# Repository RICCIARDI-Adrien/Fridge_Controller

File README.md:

# Fridge controller

A very simple controller with a light electronic BoM. It manages the fridge temperature with hardcoded thresholds and hysteresis.

## Project information

The board is powered by a PIC12F683 MCU. It samples the fridge or freezer temperature through a NTC sensor. It then controls the fridge cold unit through a 230V/12A relay.

### Hardware

The board schematic and PCB are designed with KiCad 6.

### Firmware

The microcontroller firmware is compiled with the free version of Microchip XC8 compiler.

## Photo gallery

Naked PCB :

Assembled PCB :

Connector adapters for the targeted freezer :

Transparent plastic casing (reference Deltron 479-0160-0) :

Board inside the casing with drilled holes and connector adapters :

The board controlling the freezer in a basement :

## Technical information about the Brandt UD2321 freezer

The following information have been found through reverse engineering, so be careful about their accuracy !  

The picture below shows the connector names (the names are taken from the original controller board PCB).  
There were no indications on the PCB of the pin numbers, so I assigned them myself.

Connector CN1 signals :
| Pin number | Description             |
| ---------- | ----------------------- |
| 1          | Not connected           |
| 2          | Not connected           |
| 3          | Original controller GND |
| 4          | NTC (thermal sensor)    |

Connector CN2 signals :
| Pin number | Description          |
| ---------- | -------------------- |
| 1          | Cold unit (note 1)   |
| 2          | Cold unit (note 1)   |
| 3          | Not connected        |
| 4          | Not connected        |
| 5          | Door switch (note 2) |
| 6          | 230V neutral         |
| 7          | Door switch (note 3) |
| 8          | 230V live            |

Notes :
1. Connect CN2 pins 1 and 2 to neutral to start the cold unit.
2. Door switch contact is normally closed.
3. CN2 pin 7 is connected the 230V live on the original controller board.

Connector CN3 is not populated.

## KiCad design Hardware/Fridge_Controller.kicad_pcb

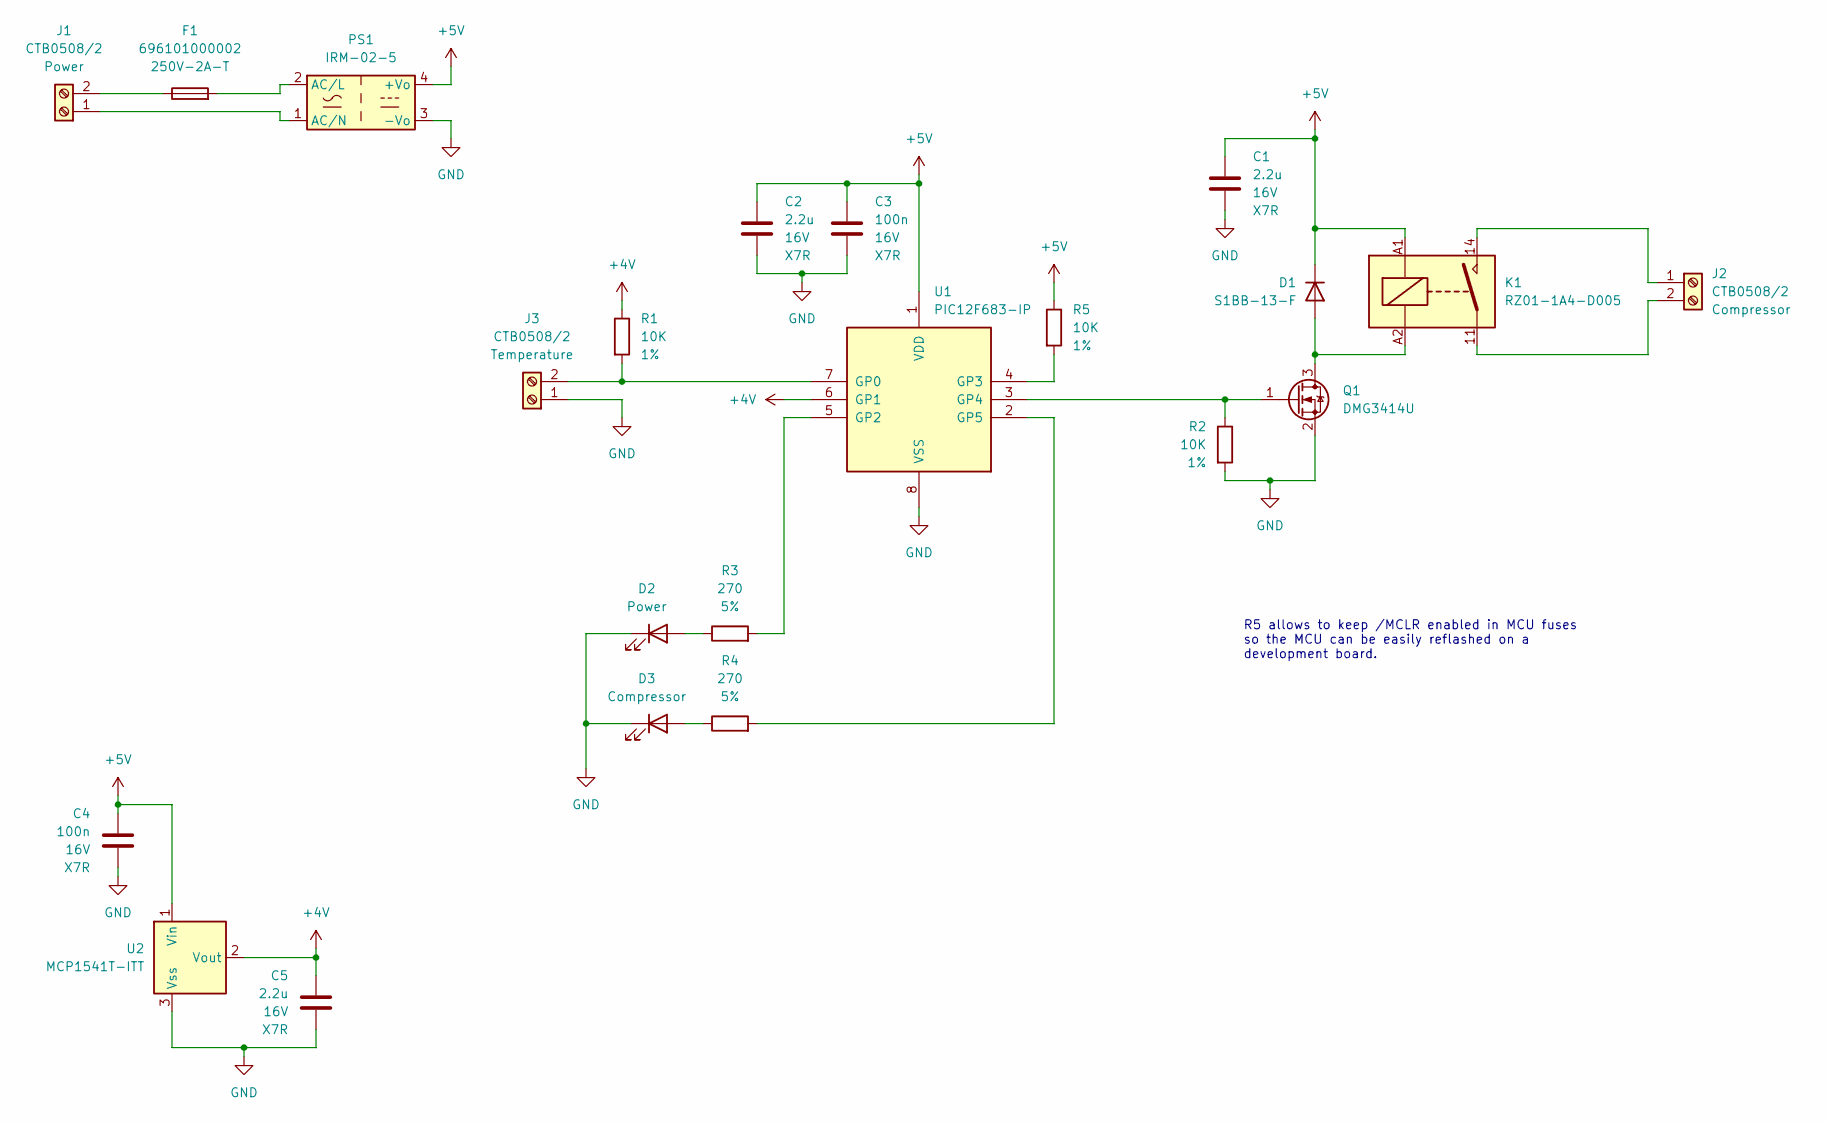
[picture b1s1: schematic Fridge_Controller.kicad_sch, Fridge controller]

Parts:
C1, C2, C5: 2.2u; C_0805_2012Metric_Pad1.18x1.45mm_HandSolder
C3, C4: 100n; C_0603_1608Metric_Pad1.08x0.95mm_HandSolder
D1: S1BB-13-F; D_SMB_Handsoldering
D2: Power; LED_D5.0mm
D3: Compressor; LED_D5.0mm
F1: 696101000002; Fuseholder_Cylinder-5x20mm_Stelvio-Kontek_PTF78_Horizontal_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
J1, J2, J3: CTB0508/2; TerminalBlock_bornier-2_P5.08mm
K1: RZ01-1A4-D005
PS1: IRM-02-5; Converter_ACDC_MeanWell_IRM-02-xx_THT
Q1: DMG3414U; SOT-23
R1, R2, R5: 10K; R_0603_1608Metric_Pad0.98x0.95mm_HandSolder
R3, R4: 270; R_1206_3216Metric_Pad1.30x1.75mm_HandSolder
U1: PIC12F683-IP; DIP-8_W7.62mm
U2: MCP1541T-ITT; SOT-23

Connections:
+4V: C5.1, R1.1, U1.6 (GP1), U2.2 (Vout)
+5V: C1.1, C2.1, C3.1, C4.1, D1.1 (K), K1.A1, PS1.4 (+Vo), R5.1, U1.1 (VDD), U2.1 (Vin)
GND: C1.2, C2.2, C3.2, C4.2, C5.2, D2.1 (K), D3.1 (K), J3.1, PS1.3 (-Vo), Q1.2 (S), R2.2, U1.8 (VSS), U2.3 (Vss)
unnamed: D1.2 (A), K1.A2, Q1.3 (D)
unnamed: D2.2 (A), R3.1
unnamed: D3.2 (A), R4.1
unnamed: F1.1, J1.2
unnamed: F1.2, PS1.2 (AC/L)
unnamed: J1.1, PS1.1 (AC/N)
unnamed: J2.1, K1.14
unnamed: J2.2, K1.11
unnamed: J3.2, R1.2, U1.7 (GP0)
unnamed: Q1.1 (G), R2.1, U1.3 (GP4)
unnamed: R3.2, U1.5 (GP2)
unnamed: R4.2, U1.2 (GP5)
unnamed: R5.2, U1.4 (GP3)

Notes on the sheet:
R5 allows to keep /MCLR enabled in MCU fuses so the MCU can be easily reflashed on a development board.

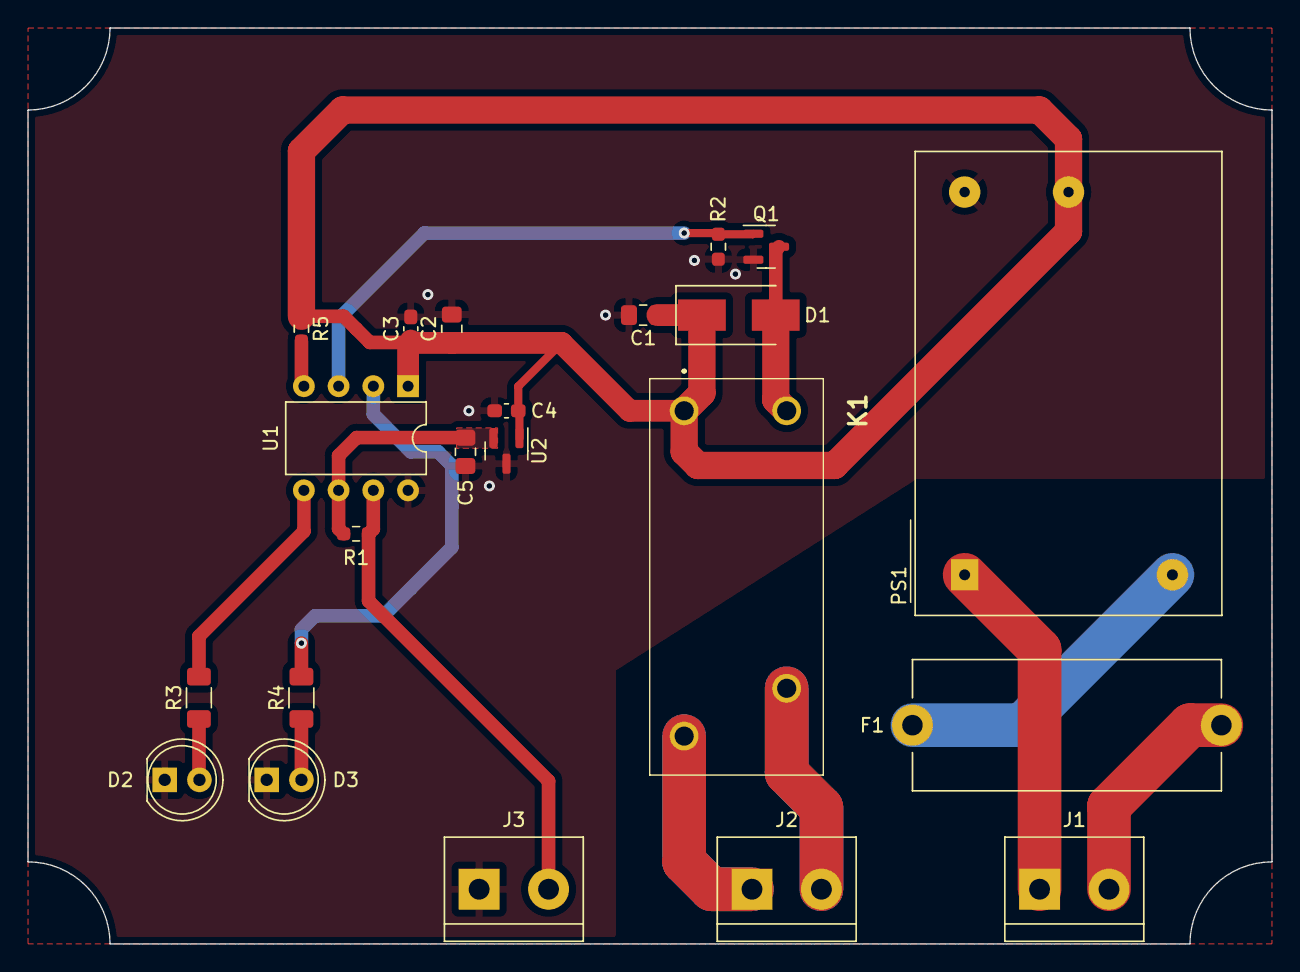
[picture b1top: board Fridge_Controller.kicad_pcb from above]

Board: 2 copper layers, 91.0 x 67.0 mm, 22 parts (0 on the bottom side), 16 nets.

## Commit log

2022-12-26 Initial commit. Added an empty KiCad project.
2022-12-26 Added MIT license.
2022-12-27 [Hardware] Added RZ01-1A4-D005 relay symbol, footprint and 3D model.
2022-12-27 [Hardware] Added schematic.
2023-01-14 [Hardware] Added fuse, fuse holder and screw terminals part references to schematics.
2023-02-02 [Hardware] Added a pull-up resistor on microcontroller /MCLR pin so the /MCLR signal can be left active in the MCU fuses and the MCU can be more easily reflashed when inserted on a development board.
2023-02-02 [Firmware] Started firmware implementation. Added microcontroller fuses configuration.
2023-02-18 [Firmware] Switched microcontroller clock speed to 1MHz and added blinking led test.
2023-02-18 [Firmware] Added GPIOs configuration, ADC module implementation and related test.
2023-02-20 [Firmware] Added the conversion to a resistance of the sampled thermistor voltage.
2023-02-20 [Firmware] Added output pins control (leds and relay).
2023-02-20 [Firmware] Added fridge compressor driving logic.
2023-02-26 [Hardware] Added PCB edges.
2023-02-26 [Hardware] Placed components on the PCB, added the logic ground planes and the keepout areas for the mains voltage.
2023-02-26 [Hardware] Routed all PCB tracks.
2023-02-26 [Hardware] Cleaned all PCB warnings.
2023-04-11 Added PCB photos to README.md.
2023-05-07 [Firmware] Adjusted the precision of the thermal sensor voltage divider value.
2023-05-09 Added pictures of the project assembly and the running board to the README.md.
2023-05-09 Added some technical information about the Brandt UD2321 freezer to the README.md.
2023-05-09 Added some details about the project and the softwares used to design it to the README.md.
